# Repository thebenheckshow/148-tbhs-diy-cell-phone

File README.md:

# 148-diy-cell-phone
Create your own cell phone

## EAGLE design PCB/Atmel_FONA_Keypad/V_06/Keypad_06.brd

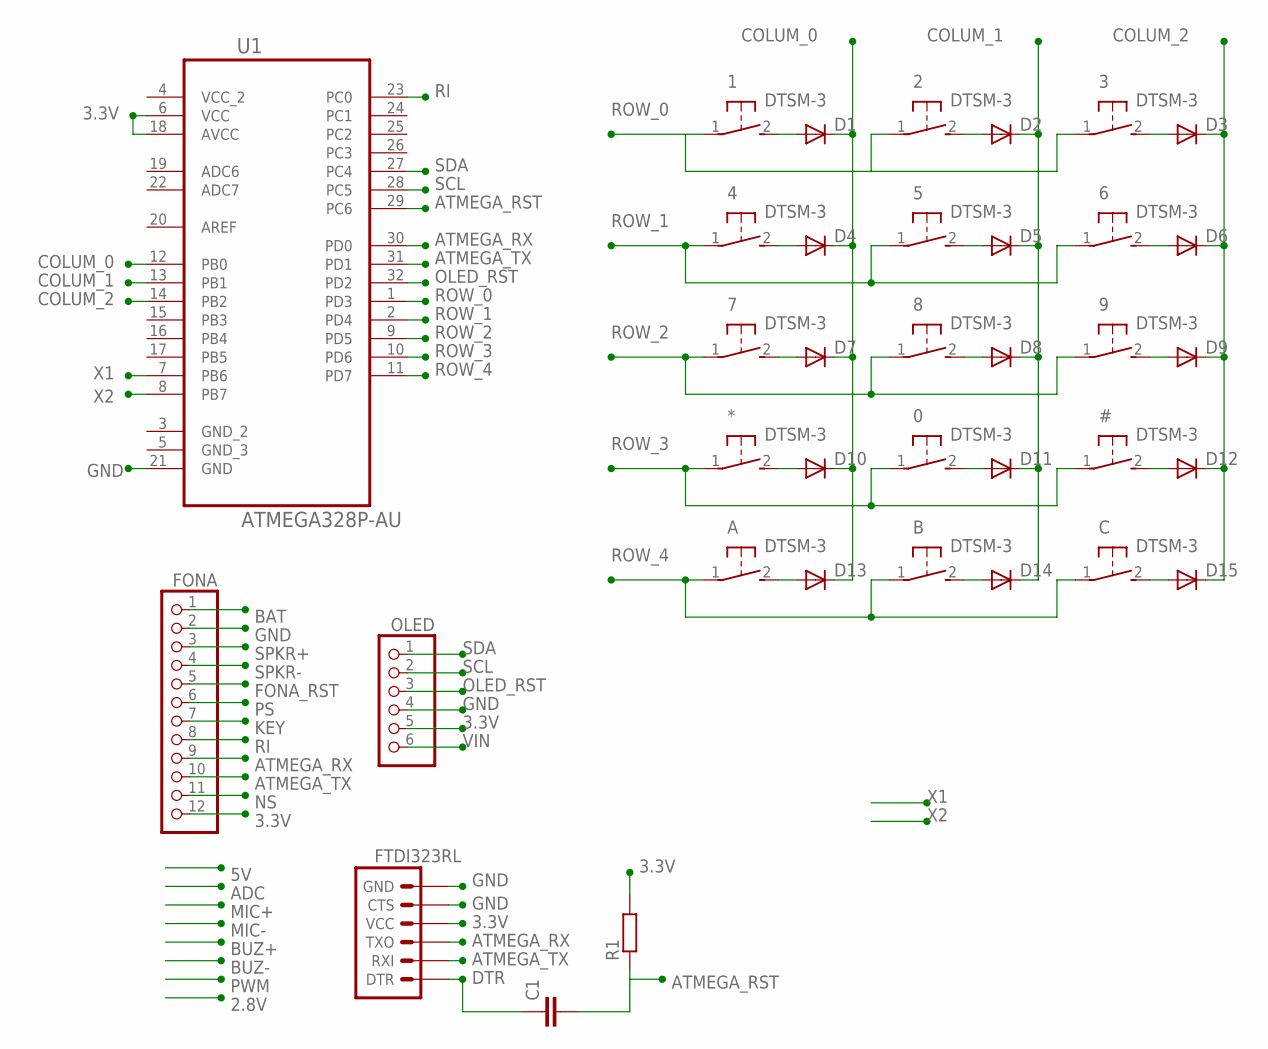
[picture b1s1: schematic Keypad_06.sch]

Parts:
0, 1, 2, 3, 4, 5, 6, 7, 8, 9: DTSM-3
#: DTSM-3
*: DTSM-3
A: DTSM-3
B: DTSM-3
C: DTSM-3
C1: C-EUC0805; C0805
D1, D2, D3, D4, D5, D6, D7, D8, D9, D10, D11, D12, D13, D14, D15: DIODE-SOD123; SOD123
FONA: PINHD-1X12; 1X12
FTDI323RL: ARDUINO_SERIAL_PROGRAMLOCK; 1X06_LOCK
OLED: PINHD-1X6; 1X06
R1: R-EU_M1206; M1206
U1: ATMEGA328P-AU; QFP80P900X900X120-32N

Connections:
1: #.2, D12.A
3: 3.2, D3.A
3.3V: FONA.12, FTDI323RL.4 (VCC), OLED.5, R1.2, U1.6 (VCC), U1.18 (AVCC)
5: 5.2, D5.A
ATMEGA_RST: C1.2, R1.1, U1.29 (PC6)
ATMEGA_RX: FONA.9, FTDI323RL.3 (TXO), U1.30 (PD0)
ATMEGA_TX: FONA.10, FTDI323RL.2 (RXI), U1.31 (PD1)
BAT: FONA.1
COLUM_0: D1.C, D4.C, D7.C, D10.C, D13.C, U1.12 (PB0)
COLUM_1: D2.C, D5.C, D8.C, D11.C, D14.C, U1.13 (PB1)
COLUM_2: D3.C, D6.C, D9.C, D12.C, D15.C, U1.14 (PB2)
DTR: C1.1, FTDI323RL.1 (DTR)
FONA_RST: FONA.5
GND: FONA.2, FTDI323RL.5 (CTS), FTDI323RL.6 (GND), OLED.4, U1.21 (GND)
KEY: FONA.7
unnamed: 1.2, D1.A
unnamed: 2.2, D2.A
unnamed: 4.2, D4.A
unnamed: 6.2, D6.A
unnamed: 7.2, D7.A
unnamed: 8.2, D8.A
unnamed: 9.2, D9.A
unnamed: *.2, D10.A
unnamed: 0.2, D11.A
unnamed: A.2, D13.A
unnamed: B.2, D14.A
unnamed: C.2, D15.A
NS: FONA.11
OLED_RST: OLED.3, U1.32 (PD2)
PS: FONA.6
RI: FONA.8, U1.23 (PC0)
ROW_0: 1.1, 2.1, 3.1, U1.1 (PD3)
ROW_1: 4.1, 5.1, 6.1, U1.2 (PD4)
ROW_2: 7.1, 8.1, 9.1, U1.9 (PD5)
ROW_3: 0.1, #.1, *.1, U1.10 (PD6)
ROW_4: A.1, B.1, C.1, U1.11 (PD7)
SCL: OLED.2, U1.28 (PC5)
SDA: OLED.1, U1.27 (PC4)
SPKR+: FONA.3
SPKR-: FONA.4
VCC_2: U1.4 (VCC_2)
VIN: OLED.6
X1: U1.7 (PB6)
X2: U1.8 (PB7)

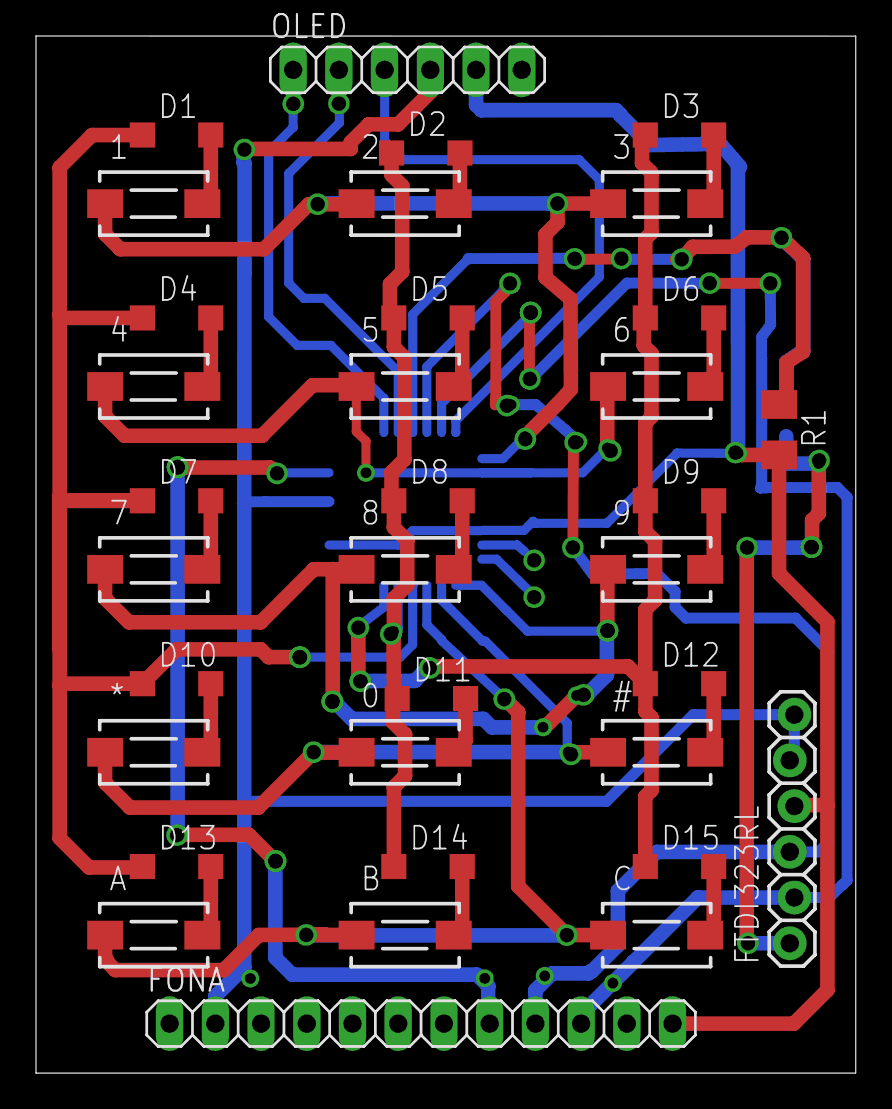
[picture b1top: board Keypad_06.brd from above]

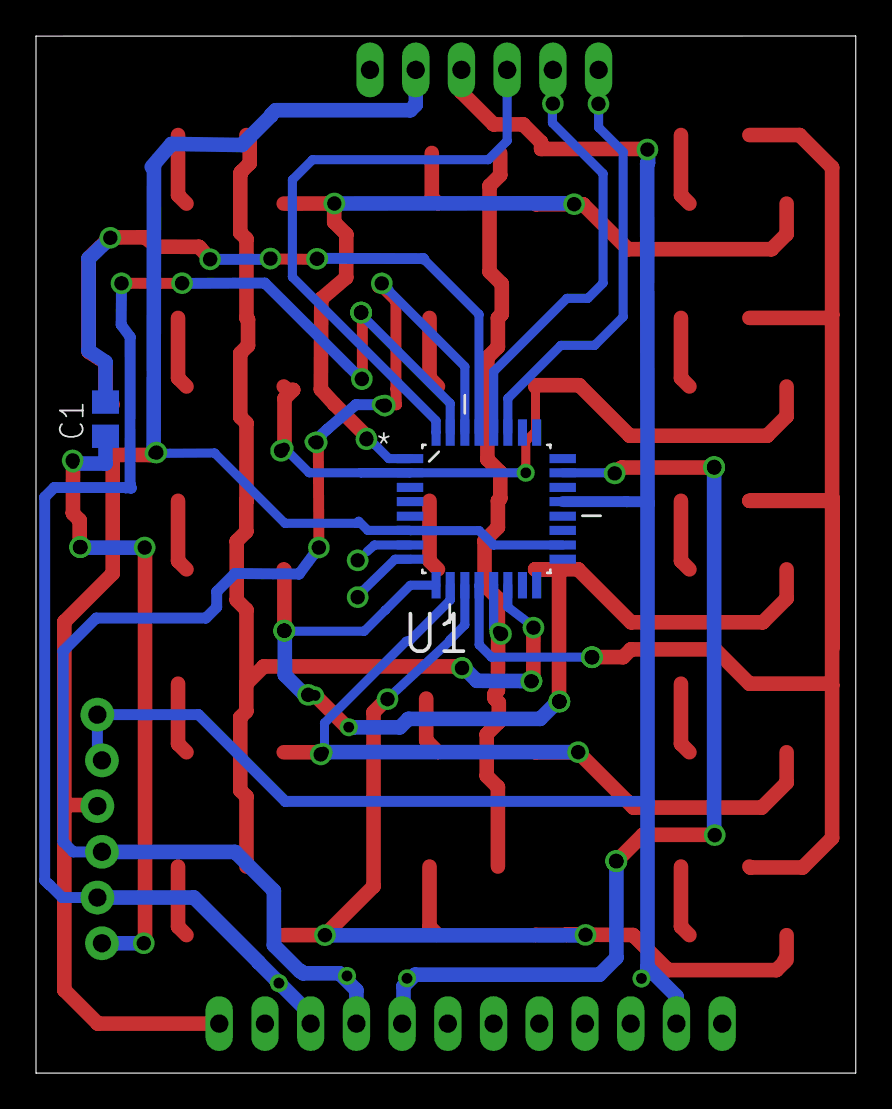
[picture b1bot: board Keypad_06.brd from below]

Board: 2 copper layers, 45.5 x 57.6 mm, 36 parts (2 on the bottom side), 33 nets.

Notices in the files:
parts and their libraries:
SparkFun-Connectors: Licensing: Creative Commons ShareAlike 4.0 International - https://creativecommons.org/licenses/by-sa/4.0
